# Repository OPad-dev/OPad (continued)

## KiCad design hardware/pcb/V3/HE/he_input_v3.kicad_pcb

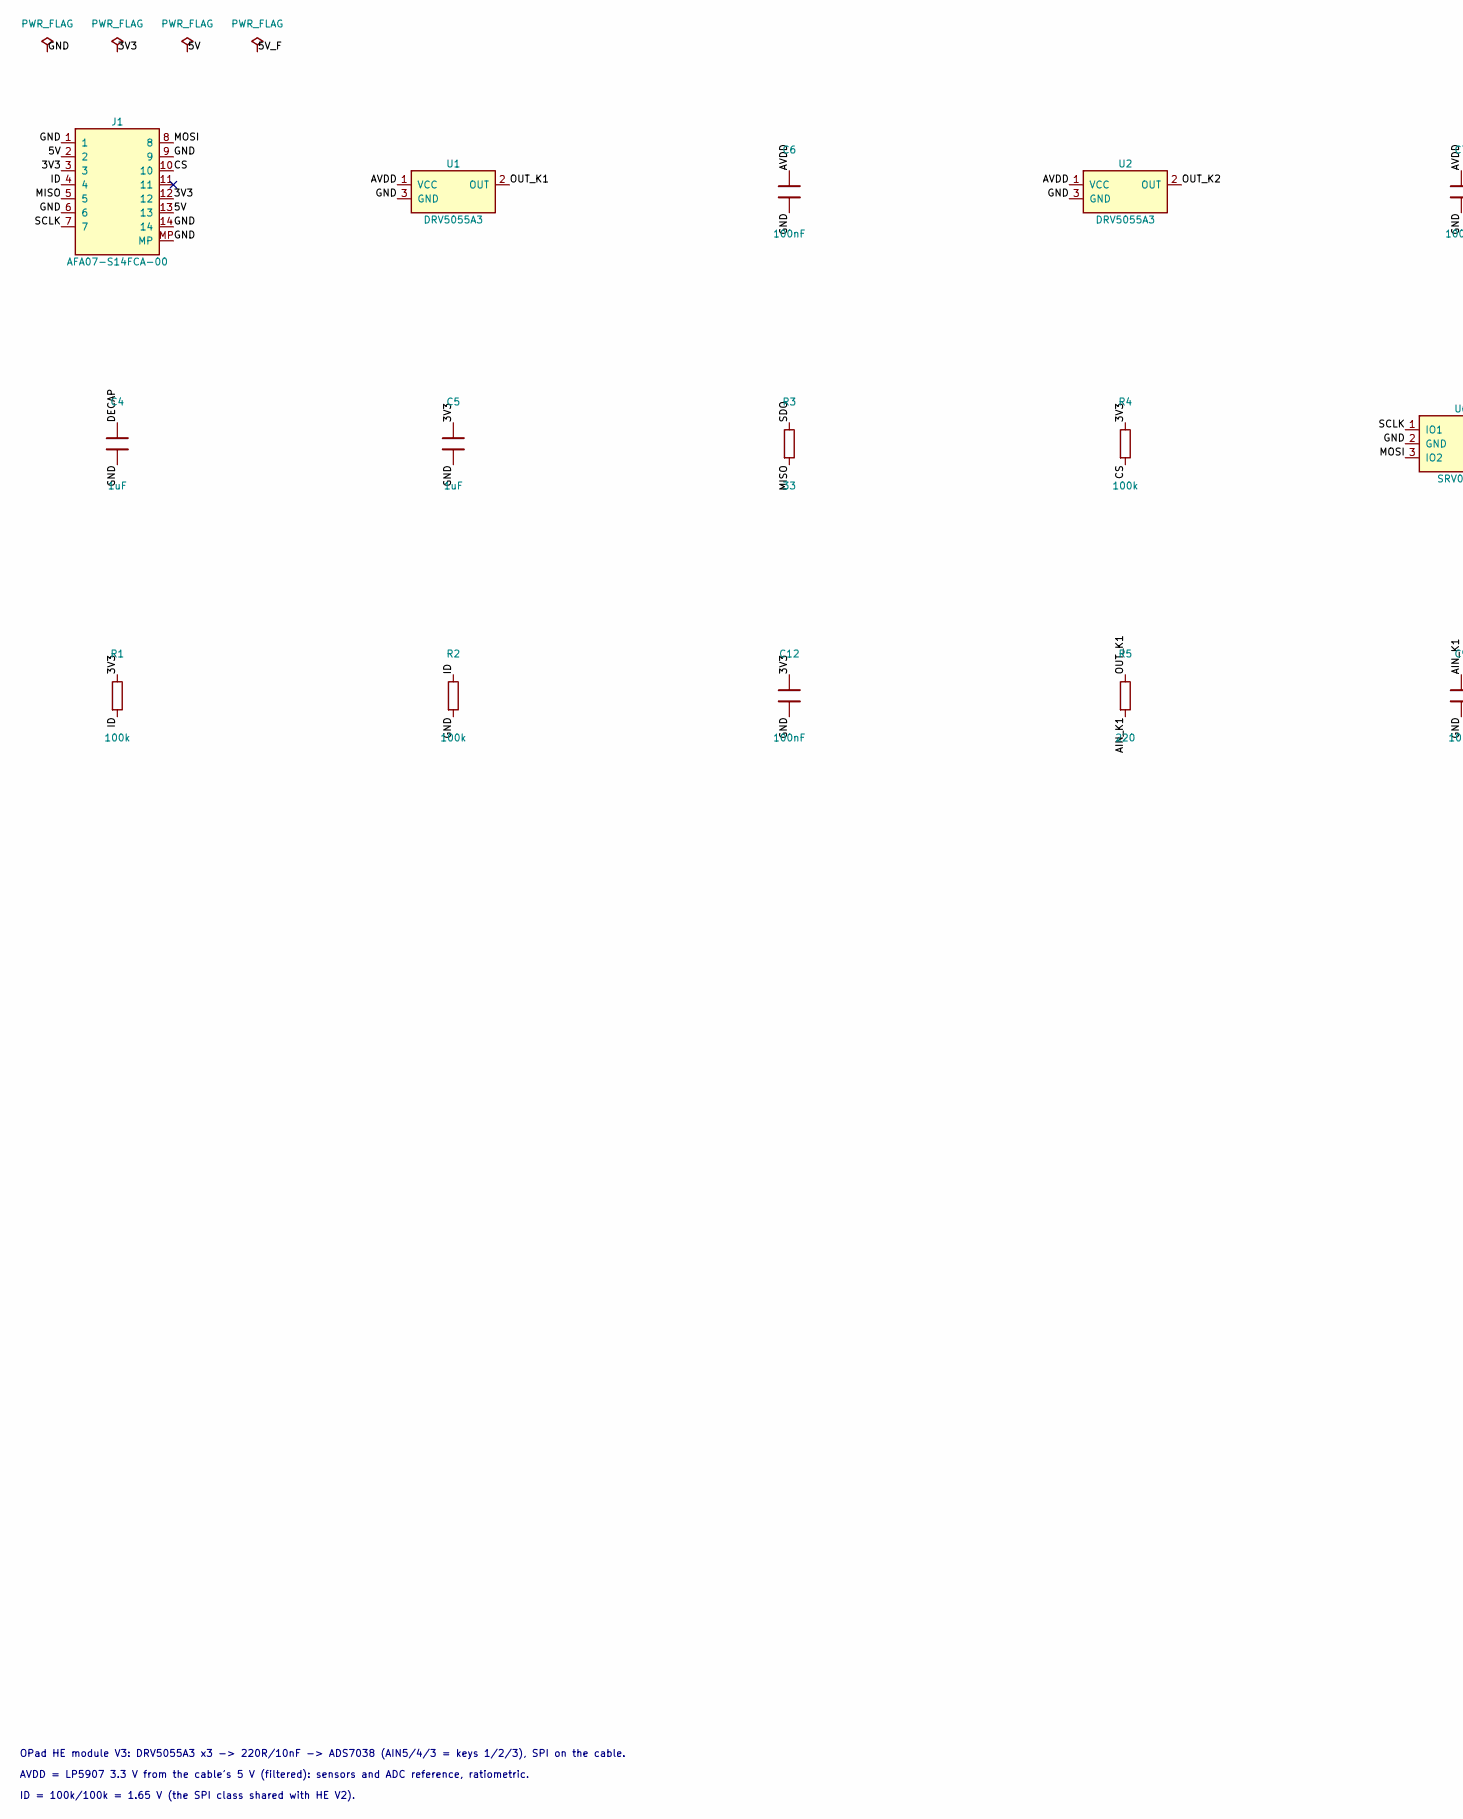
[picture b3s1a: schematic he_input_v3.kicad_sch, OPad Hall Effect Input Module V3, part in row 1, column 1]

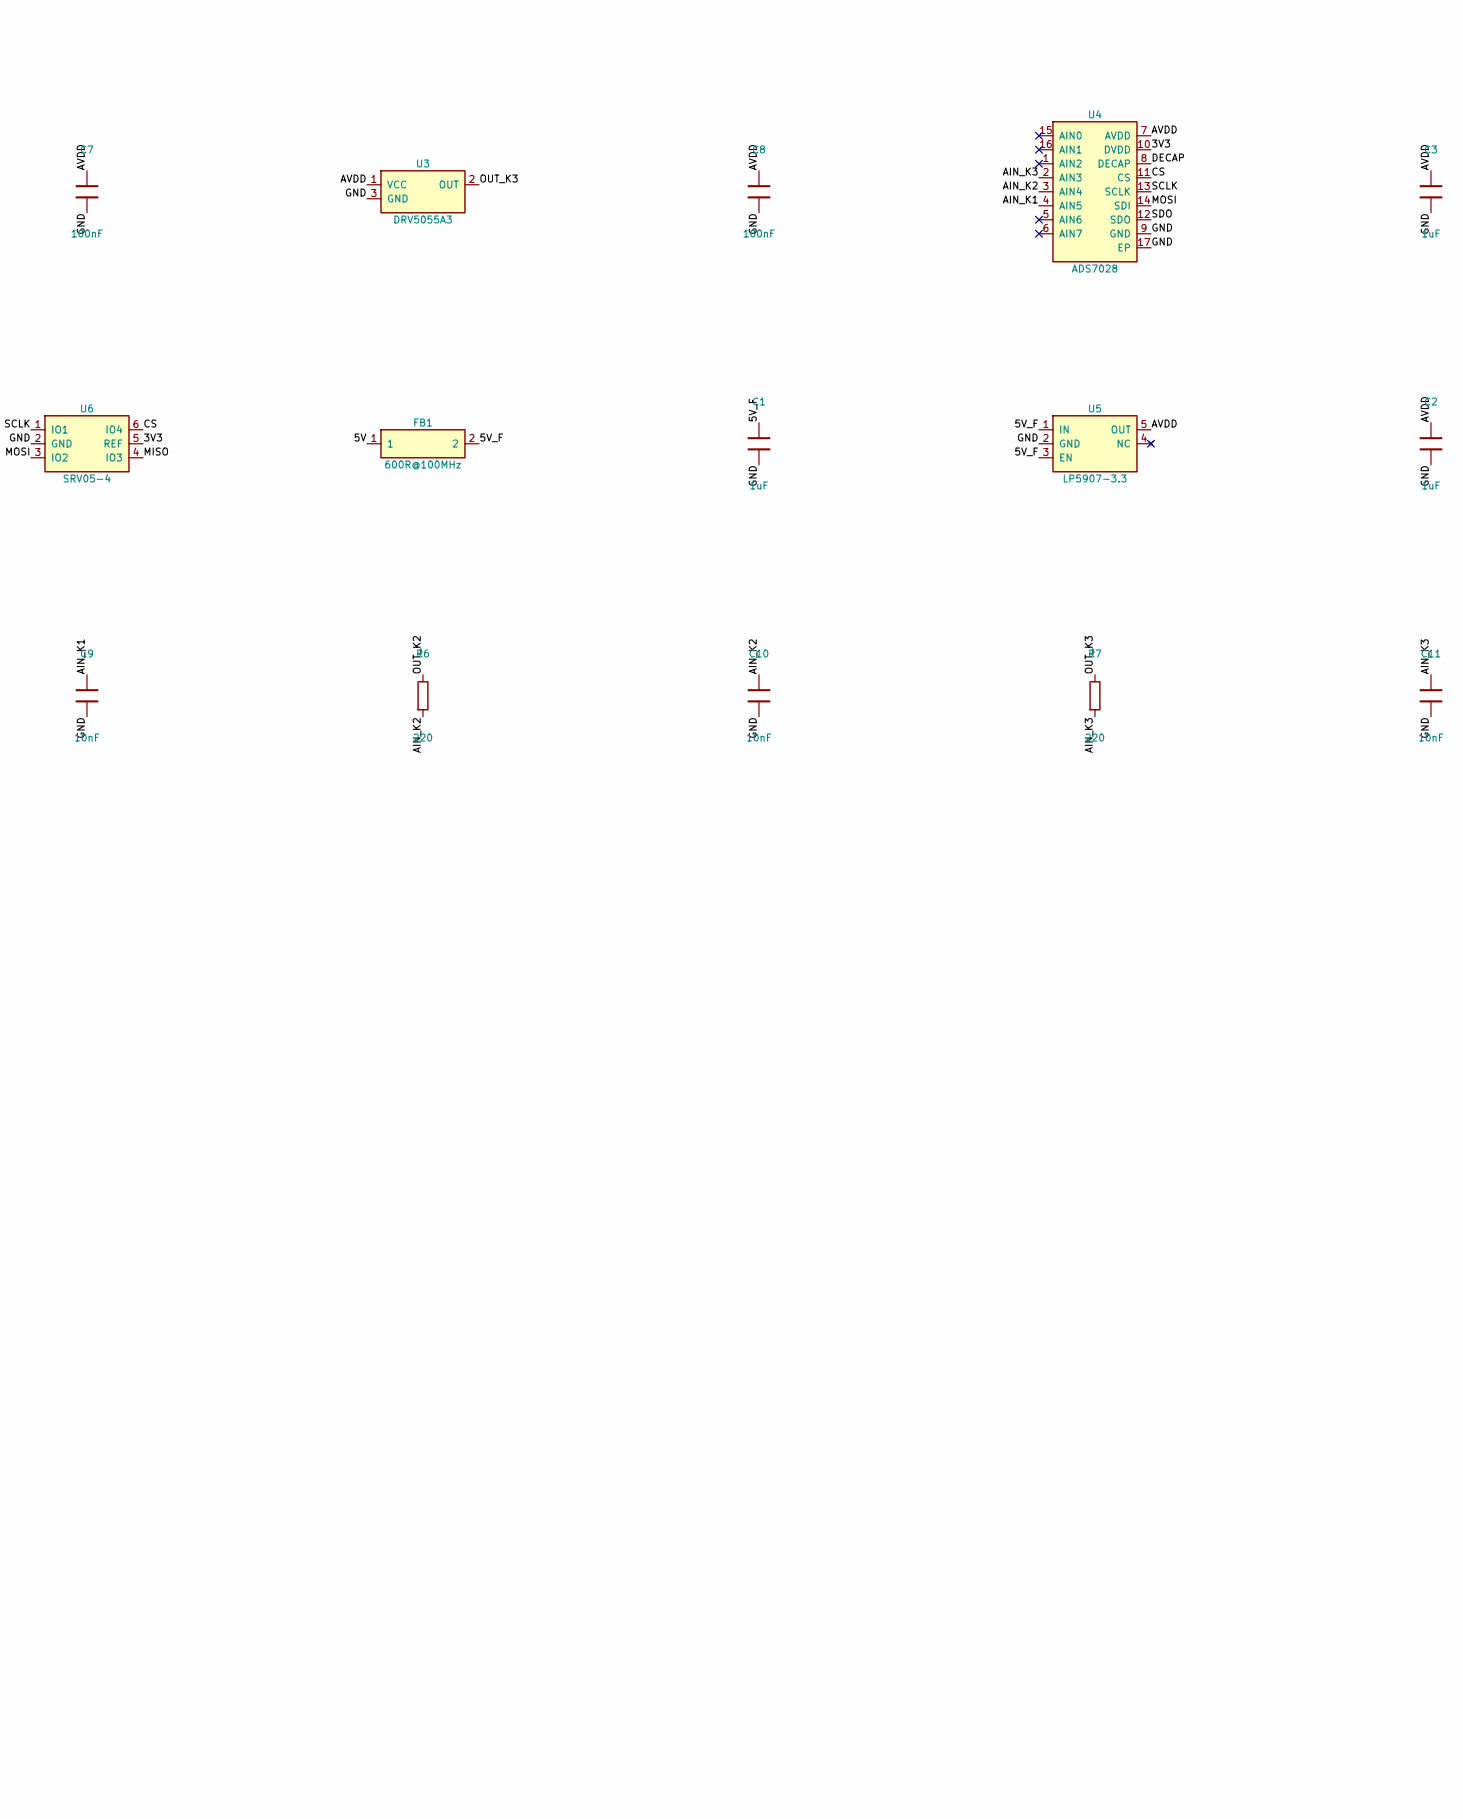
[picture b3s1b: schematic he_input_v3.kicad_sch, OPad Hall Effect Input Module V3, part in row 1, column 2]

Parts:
C1, C2, C3, C4, C5: 1uF; C_0603_1608Metric; MPN Samsung CL10A105KB8NNNC; LCSC C15849
C6, C7, C8, C12: 100nF; C_0603_1608Metric; MPN YAGEO CC0603KRX7R9BB104; LCSC C14663
C9, C10, C11: 10nF; C_0603_1608Metric; MPN FH 0603B103K500NT; LCSC C57112
FB1: 600R@100MHz; L_0603_1608Metric; MPN TDK MPZ1608S601ATA00; LCSC C107335
J1: AFA07-S14FCA-00; FFC_JUSHUO_AFA07-S14FCA_1x14-1MP_P1.0mm_Horizontal; MPN JUSHUO AFA07-S14FCA-00; LCSC C262720
R1, R2, R4: 100k; R_0603_1608Metric; MPN UNI-ROYAL 0603WAF1003T5E; LCSC C25803
R3: 33; R_0603_1608Metric; MPN UNI-ROYAL 0603WAF330JT5E; LCSC C23140
R5, R6, R7: 220; R_0603_1608Metric; MPN UNI-ROYAL 0603WAF2200T5E; LCSC C22962
U1, U2, U3: DRV5055A3; SOT-23; MPN Texas Instruments DRV5055A3QDBZR; LCSC C266128
U4: ADS7028; WQFN-16-1EP_3x3mm_P0.5mm_EP1.68mm; MPN Texas Instruments ADS7028IRTER; LCSC C880341
U5: LP5907-3.3; SOT-23-5; MPN Texas Instruments LP5907MFX-3.3/NOPB; LCSC C80670
U6: SRV05-4; SOT-23-6; MPN ProTek SRV05-4-P-T7; LCSC C85364

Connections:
/3V3: C5.1, C12.1, J1.3, J1.12, R1.1, R4.1, U4.10 (DVDD), U6.5 (REF)
/5V: FB1.1, J1.2, J1.13
/5V_F: C1.1, FB1.2, U5.1 (IN), U5.3 (EN)
/AIN_K1: C9.1, R5.2, U4.4 (AIN5)
/AIN_K2: C10.1, R6.2, U4.3 (AIN4)
/AIN_K3: C11.1, R7.2, U4.2 (AIN3)
/AVDD: C2.1, C3.1, C6.1, C7.1, C8.1, U1.1 (VCC), U2.1 (VCC), U3.1 (VCC), U4.7 (AVDD), U5.5 (OUT)
/CS: J1.10, R4.2, U4.11 (CS), U6.6 (IO4)
/DECAP: C4.1, U4.8 (DECAP)
/GND: C1.2, C2.2, C3.2, C4.2, C5.2, C6.2, C7.2, C8.2, C9.2, C10.2, C11.2, C12.2, J1.1, J1.6, J1.9, J1.14, J1.MP, R2.2, U1.3 (GND), U2.3 (GND), U3.3 (GND), U4.9 (GND), U4.17 (EP), U5.2 (GND), U6.2 (GND)
/ID: J1.4, R1.2, R2.1
/MISO: J1.5, R3.2, U6.4 (IO3)
/MOSI: J1.8, U4.14 (SDI), U6.3 (IO2)
/OUT_K1: R5.1, U1.2 (OUT)
/OUT_K2: R6.1, U2.2 (OUT)
/OUT_K3: R7.1, U3.2 (OUT)
/SCLK: J1.7, U4.13 (SCLK), U6.1 (IO1)
/SDO: R3.1, U4.12 (SDO)

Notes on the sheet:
OPad HE module V3: DRV5055A3 x3 -> 220R/10nF -> ADS7038 (AIN5/4/3 = keys 1/2/3), SPI on the cable.
AVDD = LP5907 3.3 V from the cable's 5 V (filtered): sensors and ADC reference, ratiometric.
ID = 100k/100k = 1.65 V (the SPI class shared with HE V2).

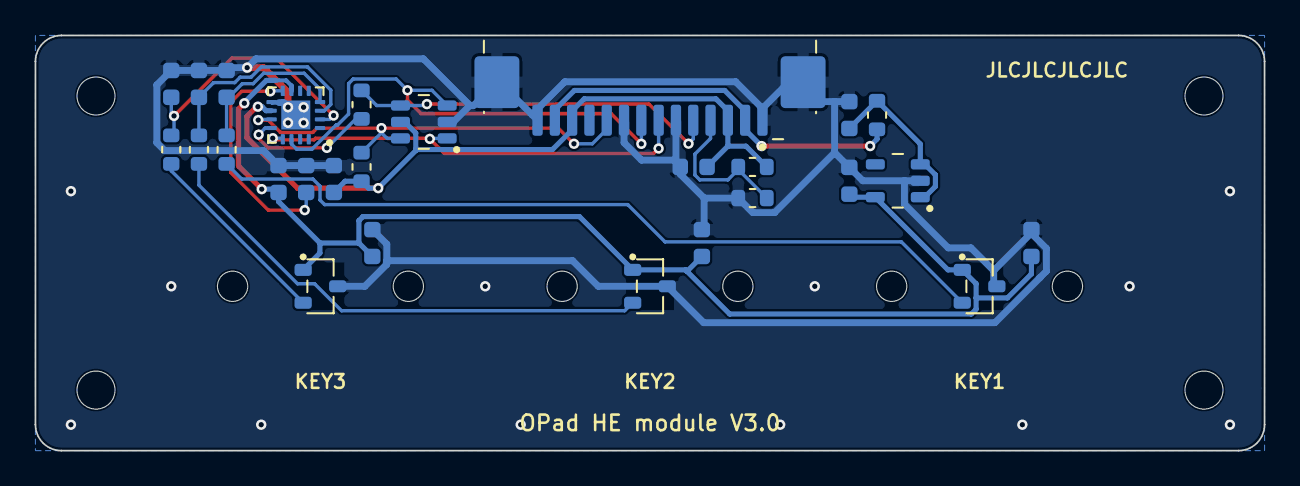
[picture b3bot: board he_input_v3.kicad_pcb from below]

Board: 2 copper layers, 71.0 x 24.0 mm, 34 parts (27 on the bottom side), 18 nets.

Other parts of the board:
H1, H2, H3, H4: MountingHole_2.2mm_M2
SW1, SW2, SW3: SW_MX_Hall_SolidCentre; SW_MX_Hall_PlateMount_SolidCentre

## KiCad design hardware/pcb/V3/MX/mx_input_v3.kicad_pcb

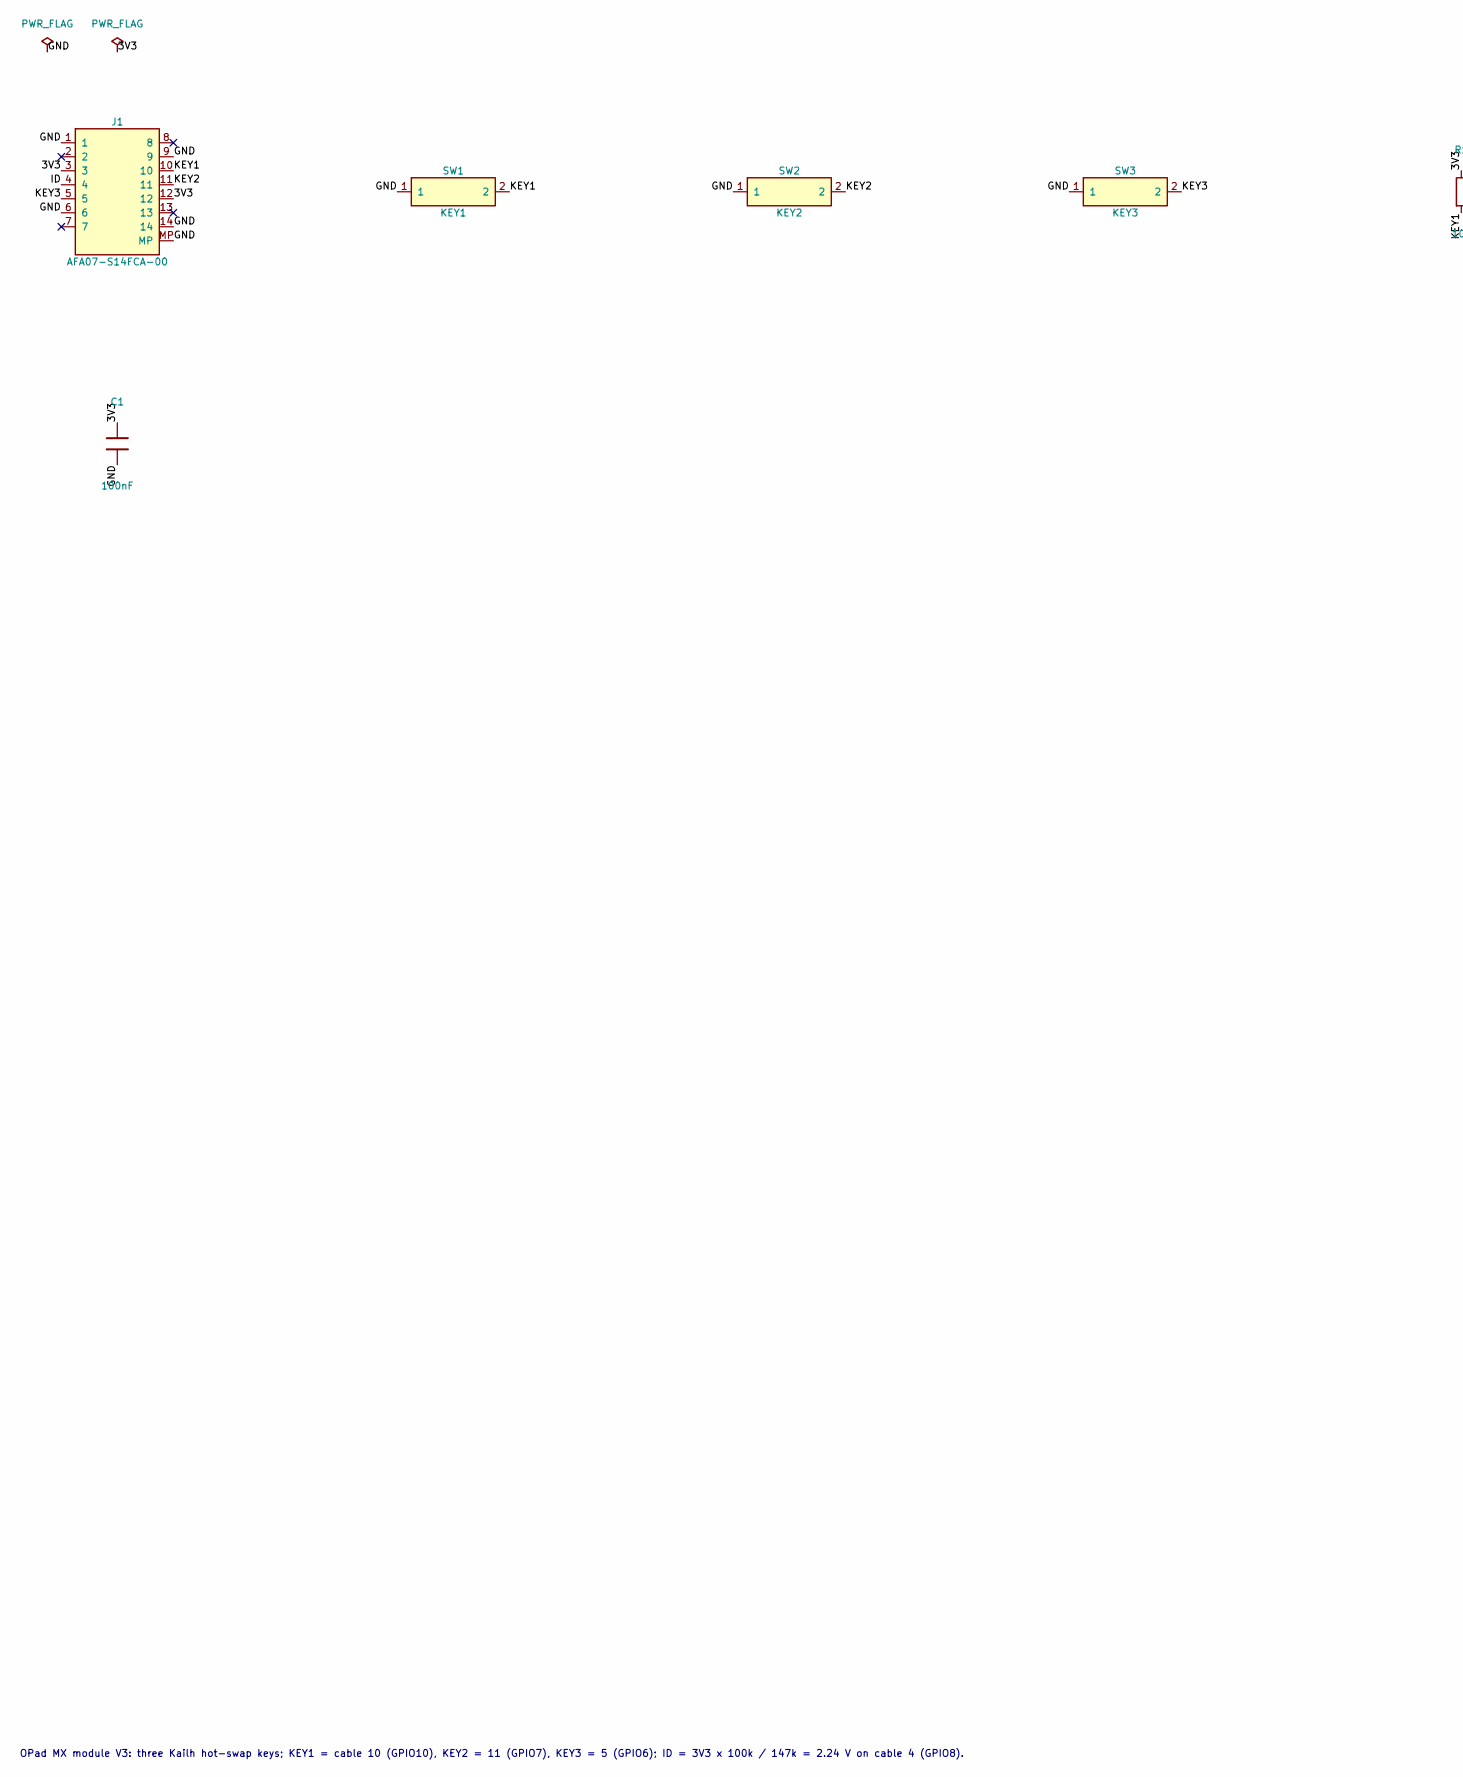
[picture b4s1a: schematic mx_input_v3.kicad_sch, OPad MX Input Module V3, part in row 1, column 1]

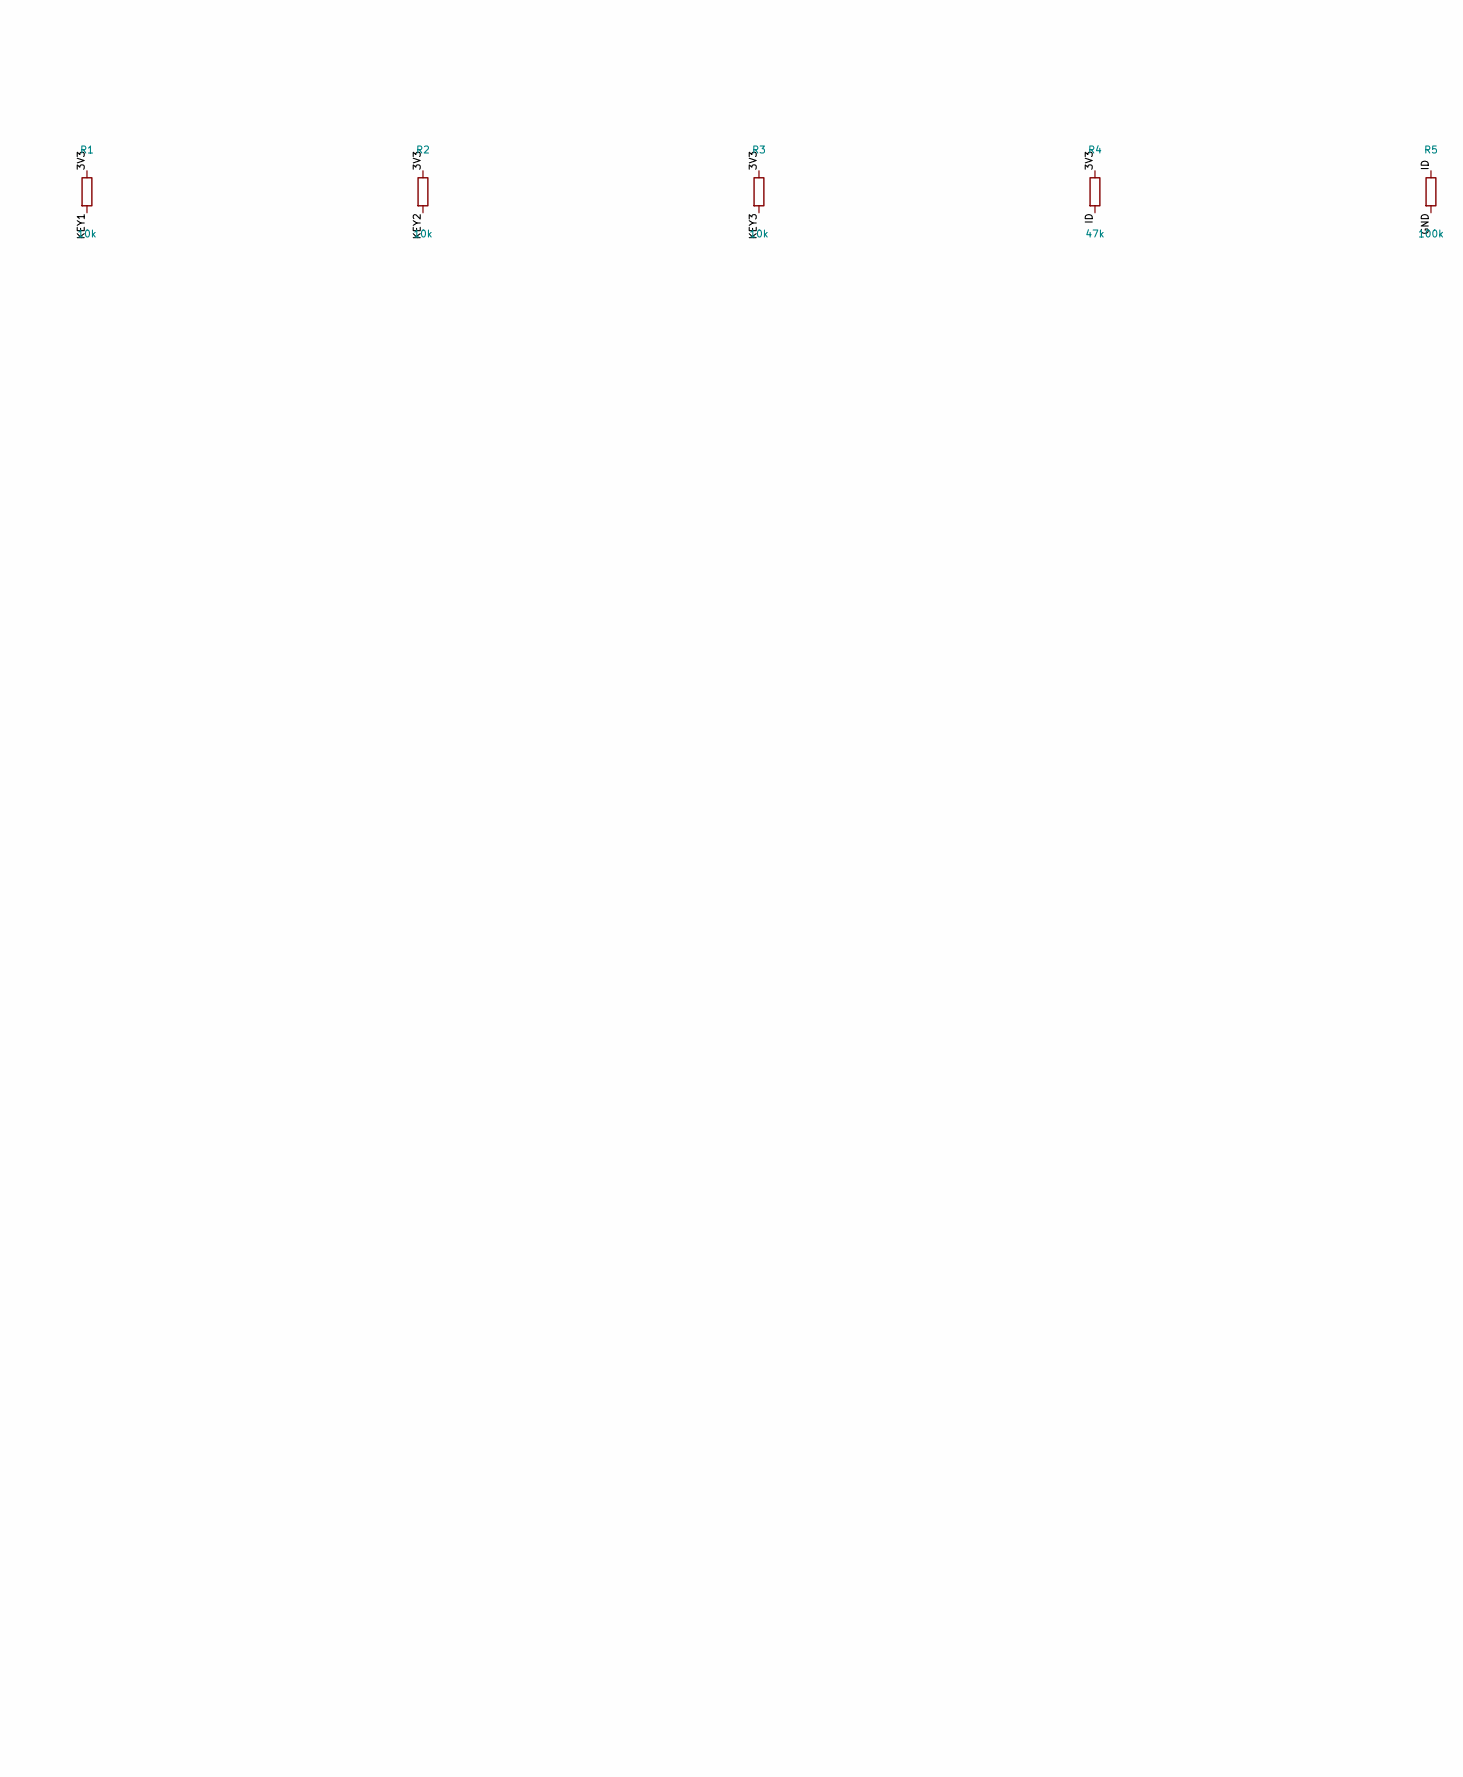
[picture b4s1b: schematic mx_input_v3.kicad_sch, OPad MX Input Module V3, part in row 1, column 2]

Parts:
C1: 100nF; C_0603_1608Metric; MPN YAGEO CC0603KRX7R9BB104; LCSC C14663
J1: AFA07-S14FCA-00; FFC_JUSHUO_AFA07-S14FCA_1x14-1MP_P1.0mm_Horizontal; MPN JUSHUO AFA07-S14FCA-00; LCSC C262720
R1, R2, R3: 10k; R_0603_1608Metric; MPN UNI-ROYAL 0603WAF1002T5E; LCSC C25804
R4: 47k; R_0603_1608Metric; MPN UNI-ROYAL 0603WAF4702T5E; LCSC C25819
R5: 100k; R_0603_1608Metric; MPN UNI-ROYAL 0603WAF1003T5E; LCSC C25803
SW1: KEY1; Kailh_CPG151101S11_MX_Hotswap_Bottom; MPN Kailh CPG151101S11; LCSC C41430893
SW2: KEY2; Kailh_CPG151101S11_MX_Hotswap_Bottom; MPN Kailh CPG151101S11; LCSC C41430893
SW3: KEY3; Kailh_CPG151101S11_MX_Hotswap_Bottom; MPN Kailh CPG151101S11; LCSC C41430893

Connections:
/3V3: C1.1, J1.3, J1.12, R1.1, R2.1, R3.1, R4.1
/GND: C1.2, J1.1, J1.6, J1.9, J1.14, J1.MP, R5.2, SW1.1, SW2.1, SW3.1
/ID: J1.4, R4.2, R5.1
/KEY1: J1.10, R1.2, SW1.2
/KEY2: J1.11, R2.2, SW2.2
/KEY3: J1.5, R3.2, SW3.2

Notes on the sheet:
OPad MX module V3: three Kailh hot-swap keys; KEY1 = cable 10 (GPIO10), KEY2 = 11 (GPIO7), KEY3 = 5 (GPIO6); ID = 3V3 x 100k / 147k = 2.24 V on cable 4 (GPIO8).

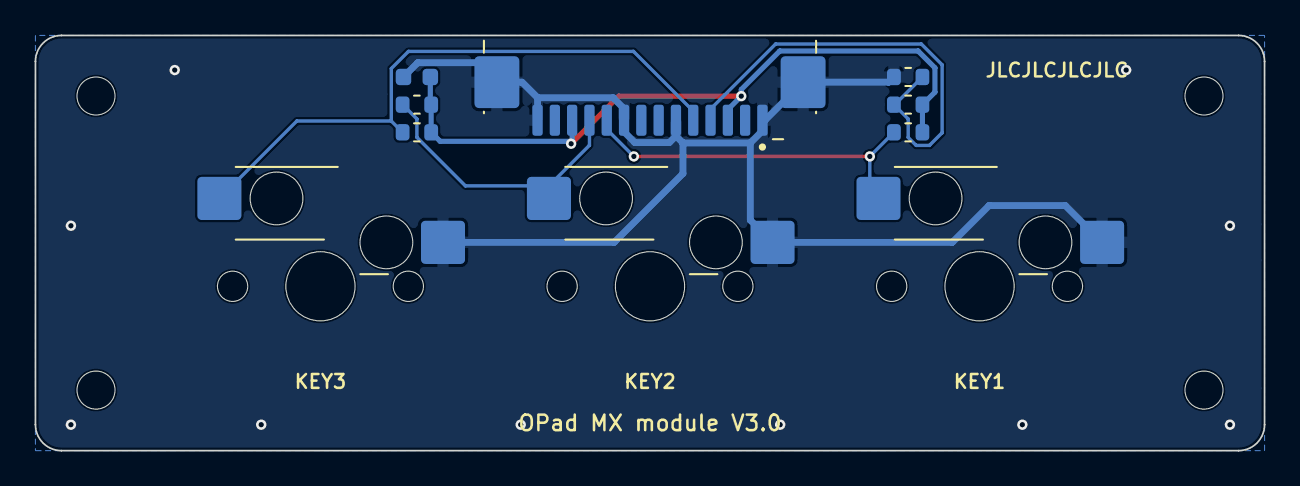
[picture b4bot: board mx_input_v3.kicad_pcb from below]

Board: 2 copper layers, 71.0 x 24.0 mm, 14 parts (10 on the bottom side), 6 nets.

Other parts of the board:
H1, H2, H3, H4: MountingHole_2.2mm_M2

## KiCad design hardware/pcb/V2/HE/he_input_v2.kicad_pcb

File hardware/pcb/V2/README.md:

# OPad V2 PCBs

| Board | Folder | Size | Status |
|---|---|---|---|
| **Hall Effect input module V2** | `HE/` | 71.05 × 24.0 mm | **Prototype, not built yet.** Firmware support not written yet (see Firmware) |

The carrier and the MX module stay at V1 (`hardware/pcb/V1/`); nothing on them changes. V2 replaces the V1.1 HE module, which is deprecated once V2 works.

## What changed from HE V1.1, and why

The V1.1 module sent the sensors' analog voltages through the cable to the ESP32-S3's own ADC. That made two kinds of noise (`docs/history/2026-10-22-he-phantom-presses.md`):

- **Constant fuzz** of ±30–40 counts per reading, from the ESP32-S3's ADC itself. The module ID resistor divider, which has no sensor, showed the same amount, and the key and ID noise did not move together (correlation +0.08).
- **Phantom spikes** of +60 to +380 counts lasting about 70 µs to 1 ms, from outside the module (USB cable or PC side), getting into the analog signals.

V2 measures the sensors **on the module** and sends numbers over SPI, so neither reaches the measurement:

| Change | Part | Why |
|---|---|---|
| ADC on the module | TI **ADS7038** (U4), 8-channel 12-bit SAR, SPI, WQFN-16 3 × 3 mm | Its reference is its own AVDD, which also powers the sensors, so the reading is **ratiometric**: a supply wobble moves the sensor output and the ADC's ruler together. It averages internally and returns 16-bit results, so the ESP32 does not have to read it more often. Only digital SPI crosses the cable. |
| Sensor supply filter | Ferrite bead FB1 (600 Ω at 100 MHz) + 10 µF C2, 100 nF at each sensor, 1 µF at the ADC's AVDD | Keeps spikes on 3V3 away from the sensors and the reference |
| Output filter per sensor | 220 Ω series + 10 nF shunt, at the ADC | TI requires a resistor before any capacitor on the DRV5055 output (datasheet §7.1.3); the 10 nF also feeds the ADC's 12 pF sampling capacitor (ADS7038 datasheet §7.3.1). Time constant 2.2 µs, so it adds no noticeable delay |
| Three keys | U1–U3 at 19.05 mm pitch | For players who do not use the middle finger as one of two keys |

Kept from V1.1:
- **Sensor:** DRV5055**A3**, bipolar, so a switch with its magnet flipped still reads (the reading goes down instead of up).
- **Sensor position:** bottom side, on the key centres, with a 3 × 3 mm copper keepout on both layers.
- **Switch standard:** the Lekker one (V1 README, "Sensor architecture").
- **Assembly:** every part on the bottom side, so JLCPCB assembles one side.

## Connector (JST SH 8-pin, V1 pinout, same cable and carrier)

| Pin | Carrier GPIO | V1.1 HE | **V2** |
|---|---|---|---|
| 1 | 3V3 | sensor supply | 3V3 → FB1 → AVDD; ADC DVDD |
| 2 | GND | ground | ground |
| 3 | GPIO10 | analog key 1 | **SPI CS** |
| 4 | GPIO7 | analog key 2 | spare, to probe pad TP1 |
| 5 | GPIO8 | ID 1.06 V | **ID 1.65 V** (100k/100k, the "Hall SPI" ID the V1 README reserved) |
| 6 | GPIO6 | probe pad | **SPI MISO** (ADC SDO through 33 Ω R3) |
| 7 | GPIO4 | probe pad | **SPI MOSI** (ADC SDI) |
| 8 | GPIO2 | probe pad | **SPI SCLK** |

ADC channels: key 1 = AIN5, key 2 = AIN4, key 3 = AIN3 (`KEY_CH` in `scripts/generate_he_v2.py`). AIN0–AIN2, AIN6 and AIN7 are unused.

## Firmware (not written yet)

V2 needs a new HE input driver before it does anything:
- **Detection:** ID 1.65 V. Until the driver exists, firmware that does not know this ID must treat the module as unknown and never as an analog HE module.
- **Reading:** SPI on GPIO10/6/4/2 to the ADS7038, auto-sequence of the three channels with averaging.
- **Third key:** the keypress path, the protocol and the app all handle two keys today.
- **Board test:** pins 6–8 become SPI, so its spare-line check must change.

## Mechanics

- **Outline:** 71.05 × 24.0 mm, 1.5 mm corners, 1.6 mm FR-4, 2 layers. 16.475 mm from each outer key centre to the board edge, as on V1.
- **Keys:** KiCad (128.475, 83.5), (147.525, 83.5), (166.575, 83.5). Plate-mount peg holes 1.75 mm at ±5.08 mm on each key.
- **Mounting holes:** 2.2 mm (M2) at (115.5, 83.5) and (179.55, 83.5), 3.5 mm from each end on the key axis.
- **J1:** centred on the middle key at the rear edge, at the V1 offset from the key line, so the same 100 mm cable reaches it.
- **The V1.1 case does not fit:** its key deck has two keys and a 52 mm module. A three-key case is needed.

## Files and toolchain

```
V2/
├── README.md
├── lib/                       osupad.pretty + osupad.kicad_sym: the V1 parts used, plus
│                              WQFN-16 (TI RTE0016C land pattern), L_0603, ADS7038, FerriteBead
├── HE/he_input_v2.*           KiCad 10 project, schematic, routed board
│   └── production/            exports (see below)
└── scripts/
    ├── generate_he_v2.py      library, schematic and placed board (overwrites them)
    ├── route_he_v2.py         Freerouting, then GND stitching vias, then zone refill
    └── export_v2.py           ERC + DRC + parity, then the fab files (reuses V1's export_production.py)
```

To rebuild (needs KiCad 10's `pcbnew` Python module and Java):

```
python3 hardware/pcb/V2/scripts/generate_he_v2.py   # placed, unrouted board
python3 hardware/pcb/V2/scripts/route_he_v2.py      # routes it (Freerouting 1.9.0)
python3 hardware/pcb/V2/scripts/export_v2.py        # checks, then hardware/pcb/V2/HE/production/
```

- `route_he_v2.py` routes a copy without zones, because Freerouting treats pours and rule areas as obstacles. It then adds the stitching vias that clear the routed copper and refills the zones.
- Freerouting 2.1.0 routes this board completely and then hangs without writing the result, so the script uses 1.9.0 (`FREEROUTING_JAR`, default `~/.kicad-mcp/freerouting-1.9.0.jar`).
- Re-running `generate_he_v2.py` discards the routing.

Checked on 2026-10-23: ERC 0, DRC 0 violations and 0 unconnected with zones refilled, schematic parity clean. U1–U3 and J1 have the same pad layout and the same CPL rotations (180° and 0°, bottom) as the built V1.1 board.

## Ordering (JLCPCB)

Upload from `HE/production/jlcpcb/`:
- `he_input_v2-gerbers.zip` for the bare board;
- `he_input_v2-BOM-JLCPCB.csv` and `he_input_v2-CPL-JLCPCB.csv` for assembly.

Order options:
- 2 layers, 1.6 mm, HASL or ENIG;
- min track and spacing 0.2 / 0.15 mm (JLCPCB's standard process does 0.1 / 0.1);
- vias 0.6 mm with a 0.3 mm hole;
- assembly side **Bottom**;
- for the order-number marker, "Specify a location": `JLCJLCJLCJLC` on the bottom silkscreen.

| Designator | Part | LCSC |
|---|---|---|
| U1, U2, U3 | TI DRV5055A3QDBZR linear Hall sensor, SOT-23 | C266128 |
| U4 | TI ADS7038QRTERQ1, WQFN-16 3 × 3 mm (automotive grade of the ADS7038, same die and pinout; the commercial ADS7038IRTER, C2871580, had 8 in stock on 2026-10-23) | C2876384 |
| J1 | JST SM08B-SRSS-TB | C160407 |
| FB1 | Sunlord GZ1608D601TF ferrite bead, 600 Ω at 100 MHz, 0603 | C1002 |
| C1, C6, C7, C8 | 100 nF 50 V X7R 0603 | C14663 |
| C2 | 10 µF 10 V X5R 0603 | C19702 |
| C3, C4, C5 | 1 µF 50 V X5R 0603 | C15849 |
| C9, C10, C11 | 10 nF 50 V X7R 0603 | C57112 |
| R1, R2 | 100 kΩ 1 % 0603 | C25803 |
| R3 | 33 Ω 5 % 0603 | C23140 |
| R5, R6, R7 | 220 Ω 1 % 0603 | C22962 |

Every LCSC number above was checked against its LCSC product page on 2026-10-23 (title, maker and part number), because V1 once shipped with a wrong one (V1 README, Ordering). TP1 is a bare probe pad: it is not in the BOM or the CPL.

**Before paying, check JLCPCB's placement preview:**
- **U1–U3:** the single lead (pin 3, GND) points to the board's front edge, as on V1.1. The generator asserts the same pad layout as the built V1.1 board.
- **U4:** pin 1 at the silkscreen dot.
- **J1:** contacts towards the inside of the board, opening at the rear edge.

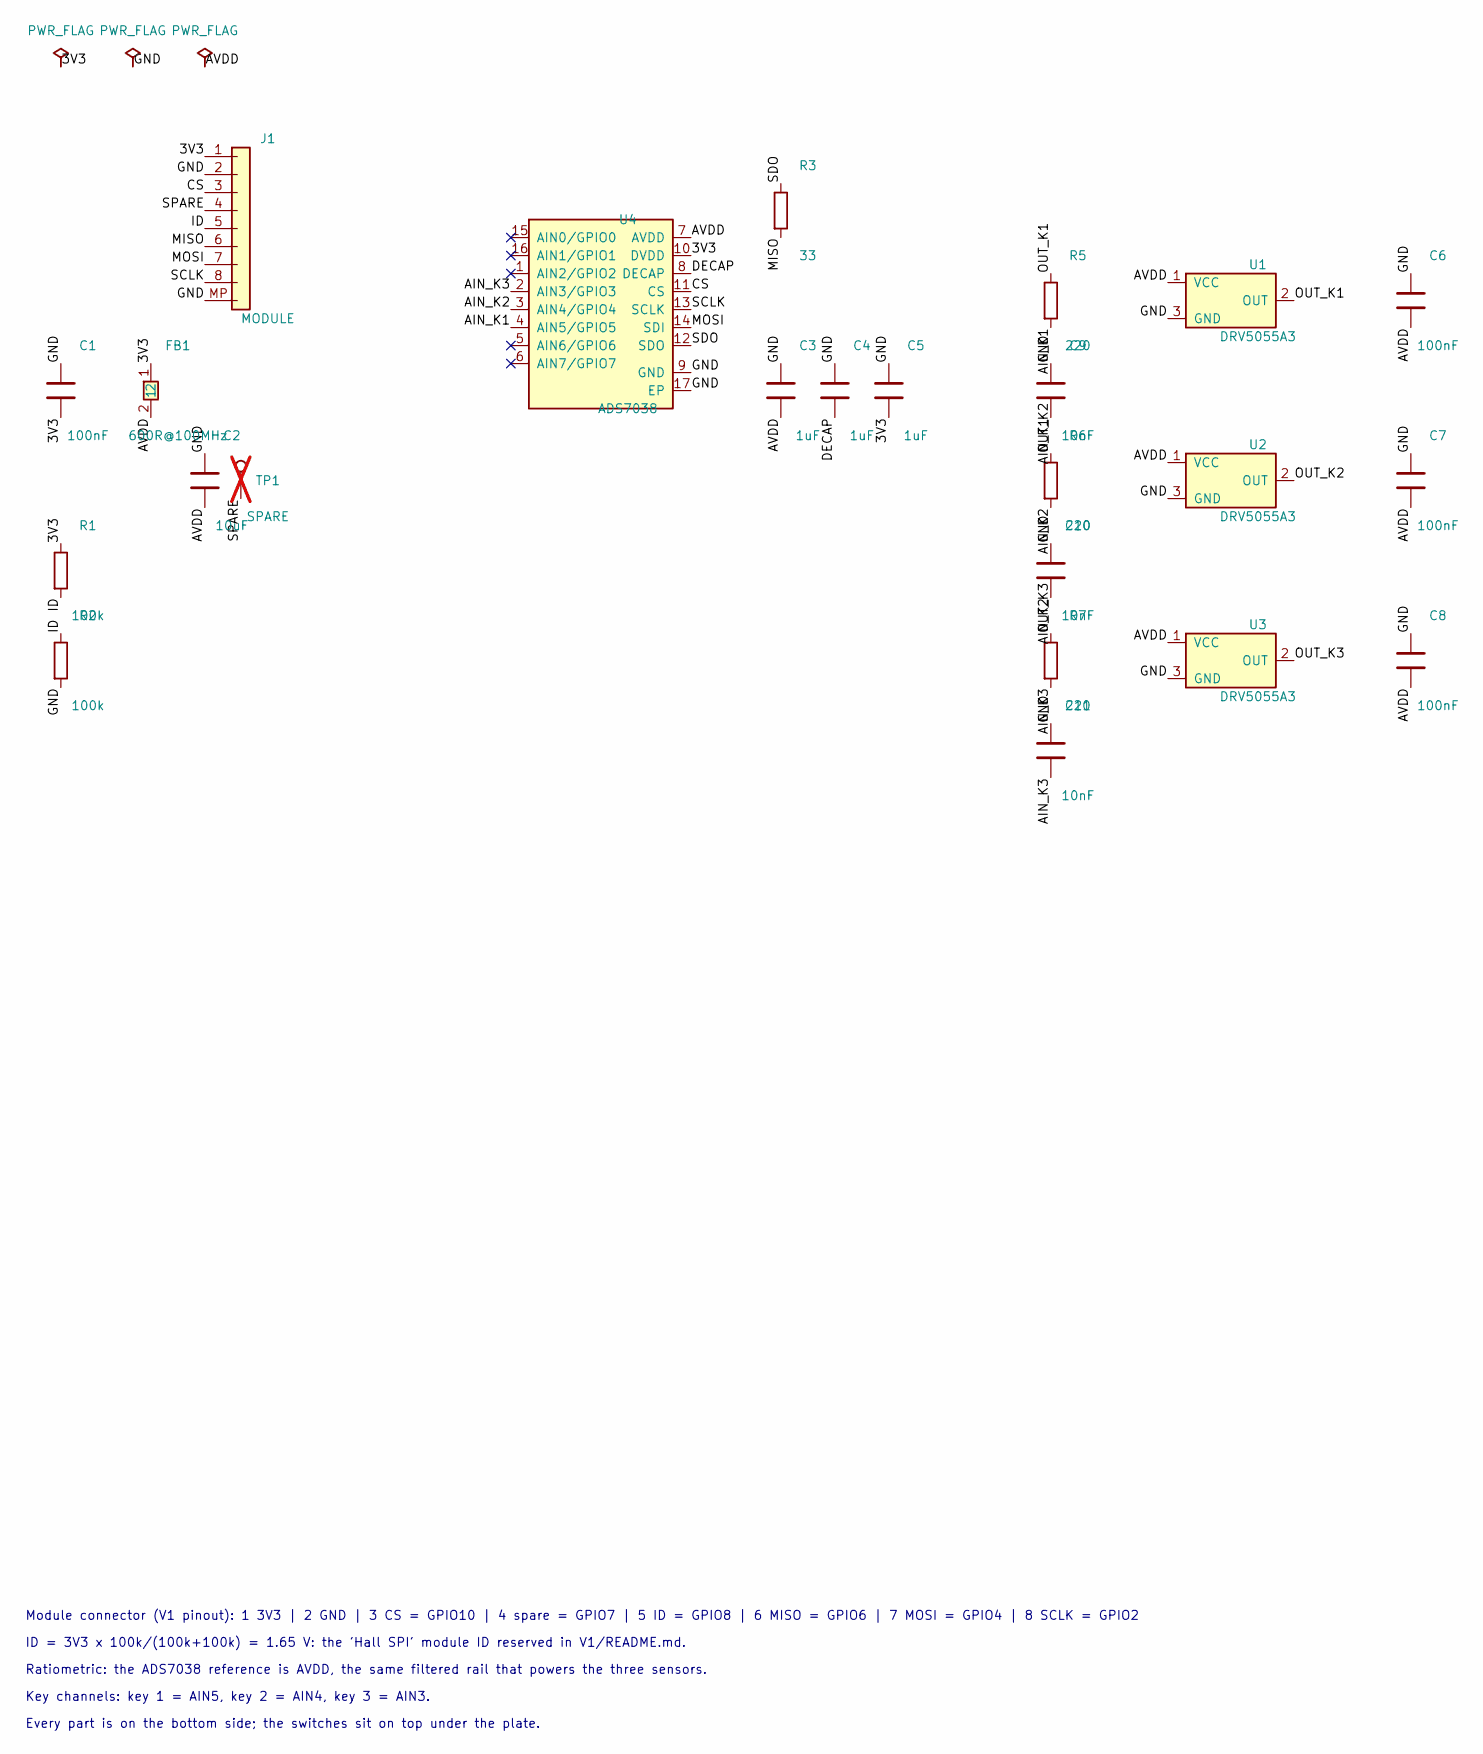
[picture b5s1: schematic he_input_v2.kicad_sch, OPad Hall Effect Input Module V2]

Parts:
C1, C6, C7, C8: 100nF; C_0603_1608Metric; MPN YAGEO CC0603KRX7R9BB104; LCSC C14663
C2: 10uF; C_0603_1608Metric; MPN Samsung CL10A106KP8NNNC; LCSC C19702
C3, C4, C5: 1uF; C_0603_1608Metric; MPN Samsung CL10A105KB8NNNC; LCSC C15849
C9, C10, C11: 10nF; C_0603_1608Metric; MPN FH 0603B103K500NT; LCSC C57112
FB1: 600R@100MHz; L_0603_1608Metric; MPN Sunlord GZ1608D601TF; LCSC C1002
J1: MODULE; JST_SH_SM08B-SRSS-TB_1x08-1MP_P1.00mm_Horizontal; MPN JST SM08B-SRSS-TB(LF)(SN); LCSC C160407
R1, R2: 100k; R_0603_1608Metric; MPN UNI-ROYAL 0603WAF1003T5E; LCSC C25803
R3: 33; R_0603_1608Metric; MPN UNI-ROYAL 0603WAF330JT5E; LCSC C23140
R5, R6, R7: 220; R_0603_1608Metric; MPN UNI-ROYAL 0603WAF2200T5E; LCSC C22962
TP1: SPARE; TestPoint_Pad_1.0x1.0mm; not fitted
U1, U2, U3: DRV5055A3; SOT-23; MPN Texas Instruments DRV5055A3QDBZR; LCSC C266128
U4: ADS7038; WQFN-16-1EP_3x3mm_P0.5mm_EP1.68mm; MPN Texas Instruments ADS7038QRTERQ1; LCSC C2876384

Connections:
/3V3: C1.2, C5.2, FB1.1, J1.1, R1.1, U4.10 (DVDD)
/AIN_K1: C9.2, R5.2, U4.4 (AIN5/GPIO5)
/AIN_K2: C10.2, R6.2, U4.3 (AIN4/GPIO4)
/AIN_K3: C11.2, R7.2, U4.2 (AIN3/GPIO3)
/AVDD: C2.2, C3.2, C6.2, C7.2, C8.2, FB1.2, U1.1 (VCC), U2.1 (VCC), U3.1 (VCC), U4.7 (AVDD)
/CS: J1.3, U4.11 (CS)
/DECAP: C4.2, U4.8 (DECAP)
/GND: C1.1, C2.1, C3.1, C4.1, C5.1, C6.1, C7.1, C8.1, C9.1, C10.1, C11.1, J1.2, J1.MP, R2.2, U1.3 (GND), U2.3 (GND), U3.3 (GND), U4.9 (GND), U4.17 (EP)
/ID: J1.5, R1.2, R2.1
/MISO: J1.6, R3.2
/MOSI: J1.7, U4.14 (SDI)
/OUT_K1: R5.1, U1.2 (OUT)
/OUT_K2: R6.1, U2.2 (OUT)
/OUT_K3: R7.1, U3.2 (OUT)
/SCLK: J1.8, U4.13 (SCLK)
/SDO: R3.1, U4.12 (SDO)
/SPARE: J1.4, TP1.1

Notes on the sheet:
Module connector (V1 pinout): 1 3V3 | 2 GND | 3 CS = GPIO10 | 4 spare = GPIO7 | 5 ID = GPIO8 | 6 MISO = GPIO6 | 7 MOSI = GPIO4 | 8 SCLK = GPIO2
ID = 3V3 x 100k/(100k+100k) = 1.65 V: the 'Hall SPI' module ID reserved in V1/README.md.
Ratiometric: the ADS7038 reference is AVDD, the same filtered rail that powers the three sensors.
Key channels: key 1 = AIN5, key 2 = AIN4, key 3 = AIN3.
Every part is on the bottom side; the switches sit on top under the plate.

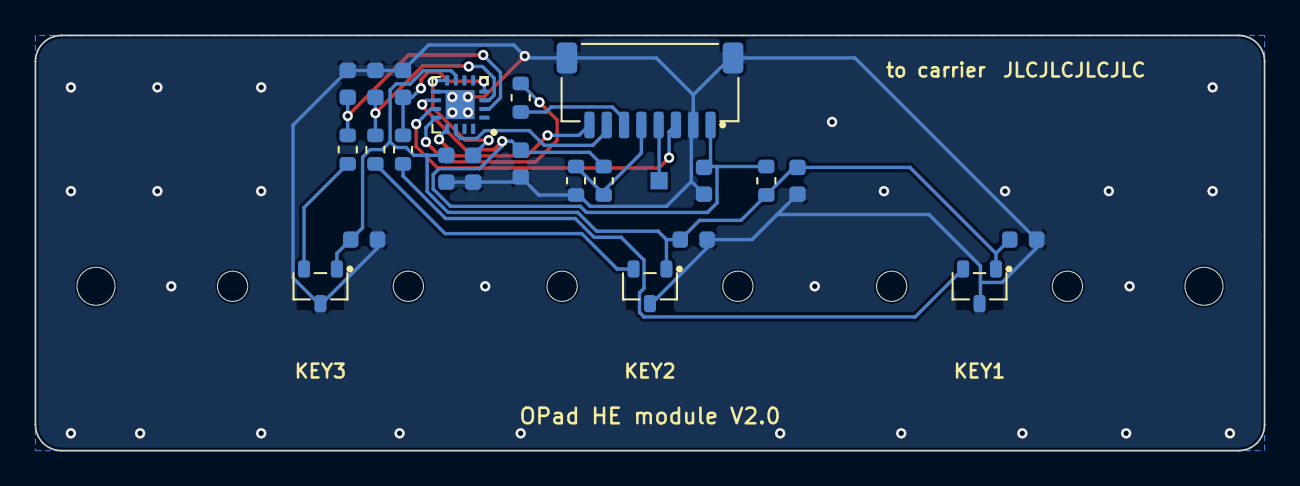
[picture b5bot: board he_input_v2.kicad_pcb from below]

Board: 2 copper layers, 71.0 x 24.0 mm, 29 parts (24 on the bottom side), 17 nets.

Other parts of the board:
H1, H2: MountingHole_2.2mm_M2
SW1, SW2, SW3: SW_MX_Hall_SolidCentre; SW_MX_Hall_PlateMount_SolidCentre

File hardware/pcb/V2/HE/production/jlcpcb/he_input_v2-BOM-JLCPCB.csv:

Comment,Designator,Footprint,LCSC Part #,MPN,Quantity
100nF,"C1,C6,C7,C8",C_0603_1608Metric,C14663,YAGEO CC0603KRX7R9BB104,4
10uF,C2,C_0603_1608Metric,C19702,Samsung CL10A106KP8NNNC,1
1uF,"C3,C4,C5",C_0603_1608Metric,C15849,Samsung CL10A105KB8NNNC,3
10nF,"C9,C10,C11",C_0603_1608Metric,C57112,FH 0603B103K500NT,3
600R@100MHz,FB1,L_0603_1608Metric,C1002,Sunlord GZ1608D601TF,1
MODULE,J1,JST_SH_SM08B-SRSS-TB_1x08-1MP_P1.00mm_Horizontal,C160407,JST SM08B-SRSS-TB(LF)(SN),1
100k,"R1,R2",R_0603_1608Metric,C25803,UNI-ROYAL 0603WAF1003T5E,2
33,R3,R_0603_1608Metric,C23140,UNI-ROYAL 0603WAF330JT5E,1
220,"R5,R6,R7",R_0603_1608Metric,C22962,UNI-ROYAL 0603WAF2200T5E,3
DRV5055A3,"U1,U2,U3",SOT-23,C266128,Texas Instruments DRV5055A3QDBZR,3
ADS7038,U4,WQFN-16-1EP_3x3mm_P0.5mm_EP1.68mm,C2876384,Texas Instruments ADS7038QRTERQ1,1
